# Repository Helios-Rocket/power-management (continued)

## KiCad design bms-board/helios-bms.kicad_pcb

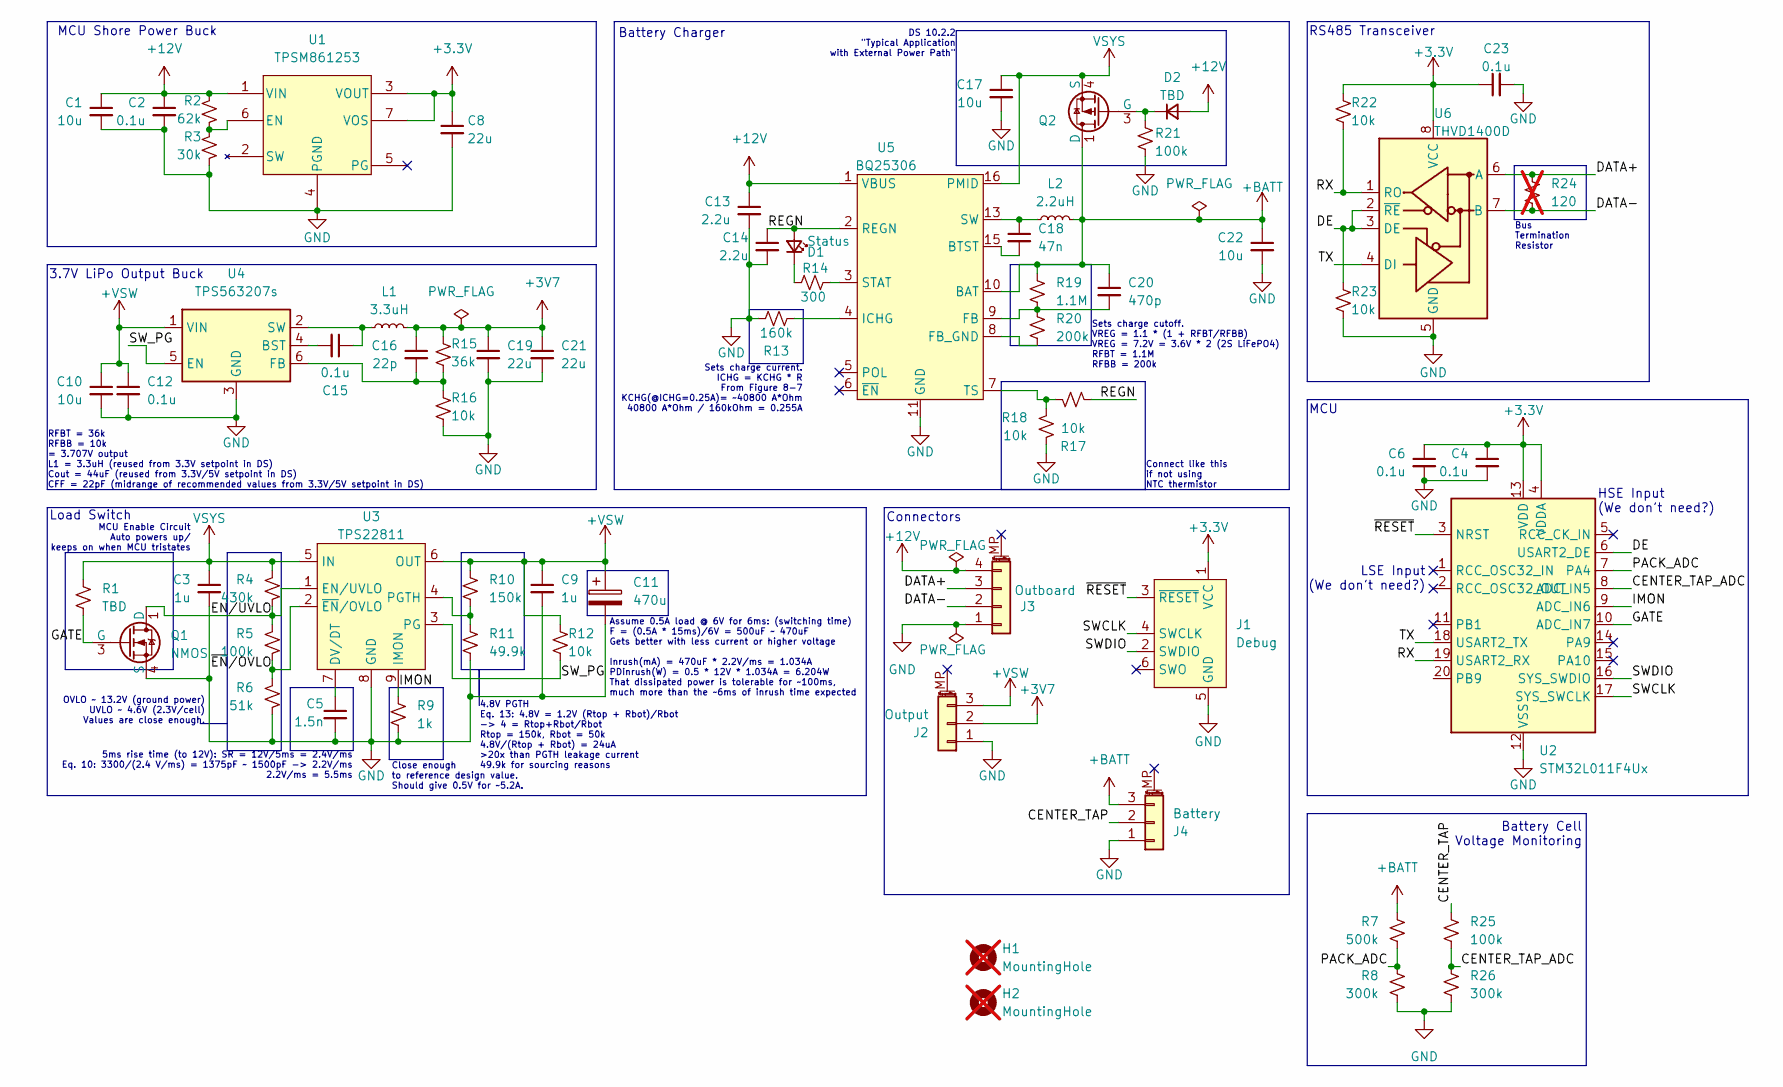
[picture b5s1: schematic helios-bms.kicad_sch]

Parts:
C1, C10, C17, C22: 10u; C_0603_1608Metric
C2, C4, C6, C12, C15, C23: 0.1u; C_0402_1005Metric
C3, C9: 1u; C_0402_1005Metric
C5: 1.5n; C_0402_1005Metric
C8, C19, C21: 22u; C_0603_1608Metric
C11: 470u; CP_Radial_D6.3mm_P2.50mm
C13, C14: 2.2u; C_0402_1005Metric
C16: 22p; C_0402_1005Metric
C18: 47n; C_0402_1005Metric
C20: 470p; C_0402_1005Metric
D1: Status; LED_0402_1005Metric
D2: TBD; D_0402_1005Metric
H1, H2: MountingHole; MountingHole_3.2mm_M3_DIN965; not fitted
J1: Debug; Tag-Connect_TC2030-IDC-NL_2x03_P1.27mm_Vertical
J2: Output; JST_ZE_SM03B-ZESS-TB_1x03-1MP_P1.50mm_Horizontal
J3: Outboard; JST_ZE_SM04B-ZESS-TB_1x04-1MP_P1.50mm_Horizontal
J4: Battery; JST_ZE_SM03B-ZESS-TB_1x03-1MP_P1.50mm_Horizontal
L1: 3.3uH; L_1008_2520Metric
L2: 2.2uH; L_0805_2012Metric
Q1: NMOS; SOT-1220_UDFN6B_TOS-L
Q2: SSM3J332R; SOT-1220_UDFN6B_TOS-L
R1: TBD; R_0402_1005Metric
R2: 62k; R_0402_1005Metric
R3: 30k; R_0402_1005Metric
R4: 430k; R_0402_1005Metric
R5, R21, R25: 100k; R_0402_1005Metric
R6: 51k; R_0402_1005Metric
R7: 500k; R_0402_1005Metric
R8, R26: 300k; R_0402_1005Metric
R9: 1k; R_0402_1005Metric
R10: 150k; R_0402_1005Metric
R11: 49.9k; R_0402_1005Metric
R12, R16, R17, R18, R22, R23: 10k; R_0402_1005Metric
R13: 160k; R_0402_1005Metric
R14: 300; R_0402_1005Metric
R15: 36k; R_0402_1005Metric
R19: 1.1M; R_0402_1005Metric
R20: 200k; R_0402_1005Metric
R24: 120; R_0402_1005Metric; not fitted
U1: TPSM861253; Texas-QFN-FCMOD-7_4x3.3mm
U2: STM32L011F4Ux; ST_UFQFPN-20_3x3mm_P0.5mm
U3: TPS22811
U4: TPS563207s; SOT-563
U5: BQ25306; WQFN-16-1EP_3x3mm_P0.5mm_EP1.68x1.68mm_ThermalVias
U6: THVD1400D; SOT-583-8

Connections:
+3.3V: C4.1, C6.1, C8.1, C23.1, J1.1 (VCC), R22.1, U1.3 (VOUT), U1.7 (VOS), U2.4 (VDDA), U2.13 (VDD), U6.8 (VCC)
+3V7: C16.1, C19.1, C21.1, J2.2, L1.2, R15.1
+12V: C1.1, C2.1, C13.1, D2.2 (A), J3.4, R2.1, U1.1 (VIN), U5.1 (VBUS)
+BATT: C20.1, C22.1, J4.3, L2.2, Q2.1 (D), Q2.2 (D), Q2.5 (D), Q2.6 (D), Q2.7 (D), R7.1, R19.1, U5.10 (BAT)
+VSW: C9.1, C10.1, C11.1, C12.1, J2.3, R10.1, R12.1, U3.6 (OUT), U4.1 (VIN)
/CENTER_TAP: J4.2, R25.1
/CENTER_TAP_ADC: R25.2, R26.1, U2.8 (ADC_IN5)
/DATA+: J3.3, R24.1, U6.6 (A)
/DATA-: J3.2, R24.2, U6.7 (B)
/DE: R23.1, U2.6 (USART2_DE), U6.2 (~RE), U6.3 (DE)
/EN/UVLO: Q1.1 (D), Q1.2 (D), Q1.5 (D), Q1.6 (D), R4.2, R5.1, U3.1 (EN/UVLO)
/GATE: Q1.3 (G), R1.2, U2.10 (ADC_IN7)
/IMON: R9.1, U2.9 (ADC_IN6), U3.9 (IMON)
/PACK_ADC: R7.2, R8.1, U2.7 (PA4)
/REGN: C14.1, D1.2 (A), R17.2, U5.2 (REGN)
/RX: R22.2, U2.19 (USART2_RX), U6.1 (RO)
/SWCLK: J1.4 (SWCLK), U2.17 (SYS_SWCLK)
/SWDIO: J1.2 (SWDIO), U2.16 (SYS_SWDIO)
/SW_PG: R12.2, U3.3 (PG), U4.5 (EN)
/TX: U2.18 (USART2_TX), U6.4 (DI)
/~EN/OVLO: R5.2, R6.1, U3.2 (~EN/OVLO)
/~RESET: J1.3 (~RESET), U2.3 (NRST)
GND: C1.2, C2.2, C3.2, C4.2, C5.2, C6.2, C8.2, C9.2, C10.2, C11.2, C12.2, C13.2, C14.2, C17.2, C19.2, C21.2, C22.2, C23.2, J1.5 (GND), J2.1, J3.1, J4.1, Q1.4 (S), R3.2, R6.2, R8.2, R9.2, R11.2, R13.2, R16.2, R18.2, R21.2, R23.2, R26.2, U1.4 (PGND), U2.12 (VSS), U3.8 (GND), U4.3 (GND), U5.11 (GND), U5.12 (GND), U5.17 (GND), U6.5 (GND)
unnamed: C18.1, L2.1, U5.13 (SW), U5.14 (SW)
unnamed: D1.1 (K), R14.1
unnamed: D2.1 (K), Q2.3 (G), R21.1
unnamed: R2.2, R3.1, U1.6 (EN)
unnamed: C5.1, U3.7 (DV/DT)
unnamed: R10.2, R11.1, U3.4 (PGTH)
unnamed: C15.2, U4.4 (BST)
unnamed: C16.2, R15.2, R16.1, U4.6 (FB)
unnamed: C15.1, L1.1, U4.2 (SW)
unnamed: C18.2, U5.15 (BTST)
unnamed: C20.2, R19.2, R20.1, U5.9 (FB)
unnamed: R20.2, U5.8 (FB_GND)
unnamed: R13.1, U5.4 (ICHG)
unnamed: R14.2, U5.3 (STAT)
unnamed: R17.1, R18.1, U5.7 (TS)
VSYS: C3.1, C17.1, Q2.4 (S), Q2.8 (S), R1.1, R4.1, U3.5 (IN), U5.16 (PMID)

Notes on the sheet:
3.7V LiPo Output Buck
LSE Input (We don't need?)
MCU Shore Power Buck
Load Switch
4.8V PGTH Eq. 13: 4.8V = 1.2V (Rtop + Rbot)/Rbot -> 4 = Rtop+Rbot/Rbot Rtop = 150k, Rbot = 50k 4.8V/(Rtop + Rbot) = 24uA >20x than PGTH leakage current 49.9k for sourcing reasons
OVLO ~ 13.2V (ground power) UVLO ~ 4.6V (2.3V/cell) Values are close enough.
DS 10.2.2 "Typical Application with External Power Path"
Sets charge cutoff. VREG = 1.1 * (1 + RFBT/RFBB) VREG = 7.2V = 3.6V * 2 (2S LiFePO4) RFBT = 1.1M RFBB = 200k
RFBT = 36k RFBB = 10k = 3.707V output L1 = 3.3uH (reused from 3.3V setpoint in DS) Cout = 44uF (reused from 3.3V/5V setpoint in DS) CFF = 22pF (midrange of recommended values from 3.3V/5V setpoint in DS)
Close enough to reference design value. Should give 0.5V for ~5.2A.
Sets charge current. ICHG = KCHG * R From Figure 8-7 KCHG(@ICHG=0.25A)= ~40800 A*Ohm 40800 A*Ohm / 160kOhm = 0.255A
MCU Enable Circuit Auto powers up/ keeps on when MCU tristates
Connect like this if not using NTC thermistor
HSE Input (We don't need?)
RS485 Transceiver
MCU
Bus Termination Resistor
5ms rise time (to 12V): SR = 12V/5ms = 2.4V/ms Eq. 10: 3300/(2.4 V/ms) = 1375pF ~ 1500pF -> 2.2V/ms 2.2V/ms = 5.5ms
Battery Cell Voltage Monitoring
Assume 0.5A load @ 6V for 6ms: (switching time) F = (0.5A * 15ms)/6V = 500uF ~ 470uF Gets better with less current or higher voltage Inrush(mA) = 470uF * 2.2V/ms = 1.034A PDinrush(W) = 0.5 * 12V * 1.034A = 6.204W That dissipated power is tolerable for ~100ms, much more than the ~6ms of inrush time 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
Battery Charger
Connectors

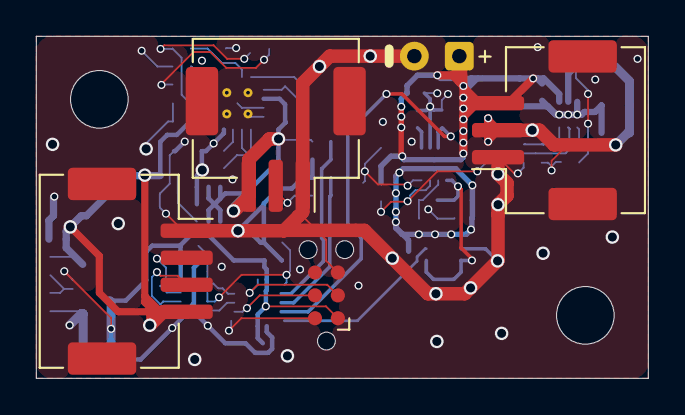
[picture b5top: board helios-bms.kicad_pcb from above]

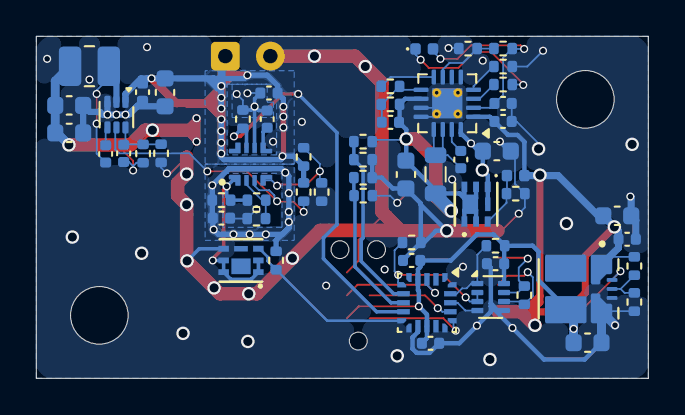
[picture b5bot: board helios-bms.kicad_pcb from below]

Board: 4 copper layers, 34.0 x 19.0 mm, 66 parts (59 on the bottom side), 39 nets.

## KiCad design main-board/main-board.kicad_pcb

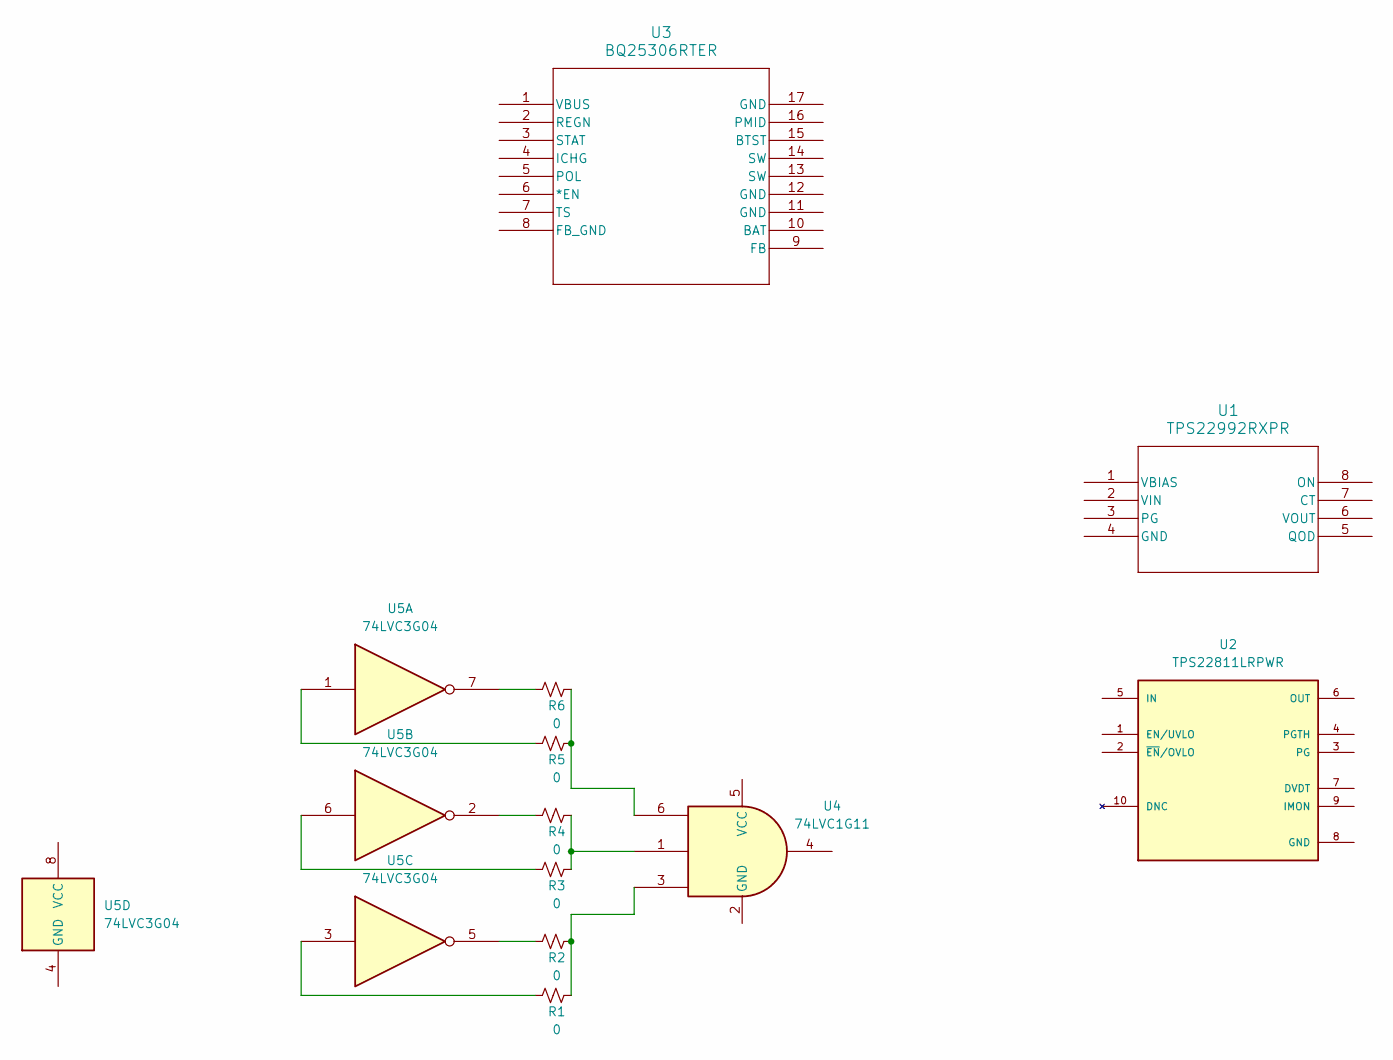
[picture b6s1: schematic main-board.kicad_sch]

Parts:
R1, R2, R3, R4, R5, R6: 0; R_0402_1005Metric
U1: TPS22992RXPR; WQFN8_RXP_TEX
U2: TPS22811LRPWR; IC_TPS22811LRPWR; PARTREV A
U3: BQ25306RTER; WQFN16_RTE_TEX
U4: 74LVC1G11; X2-DFN1010-6
U5: 74LVC3G04; SOT833-1

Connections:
unnamed: R1.1, U5.3
unnamed: R1.2, R2.2, U4.3
unnamed: R2.1, U5.5
unnamed: R3.1, U5.6
unnamed: R3.2, R4.2, U4.1
unnamed: R4.1, U5.2
unnamed: R5.1, U5.1
unnamed: R5.2, R6.2, U4.6
unnamed: R6.1, U5.7

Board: 2 copper layers, 11 parts (0 on the bottom side), 9 nets, no tracks yet.
